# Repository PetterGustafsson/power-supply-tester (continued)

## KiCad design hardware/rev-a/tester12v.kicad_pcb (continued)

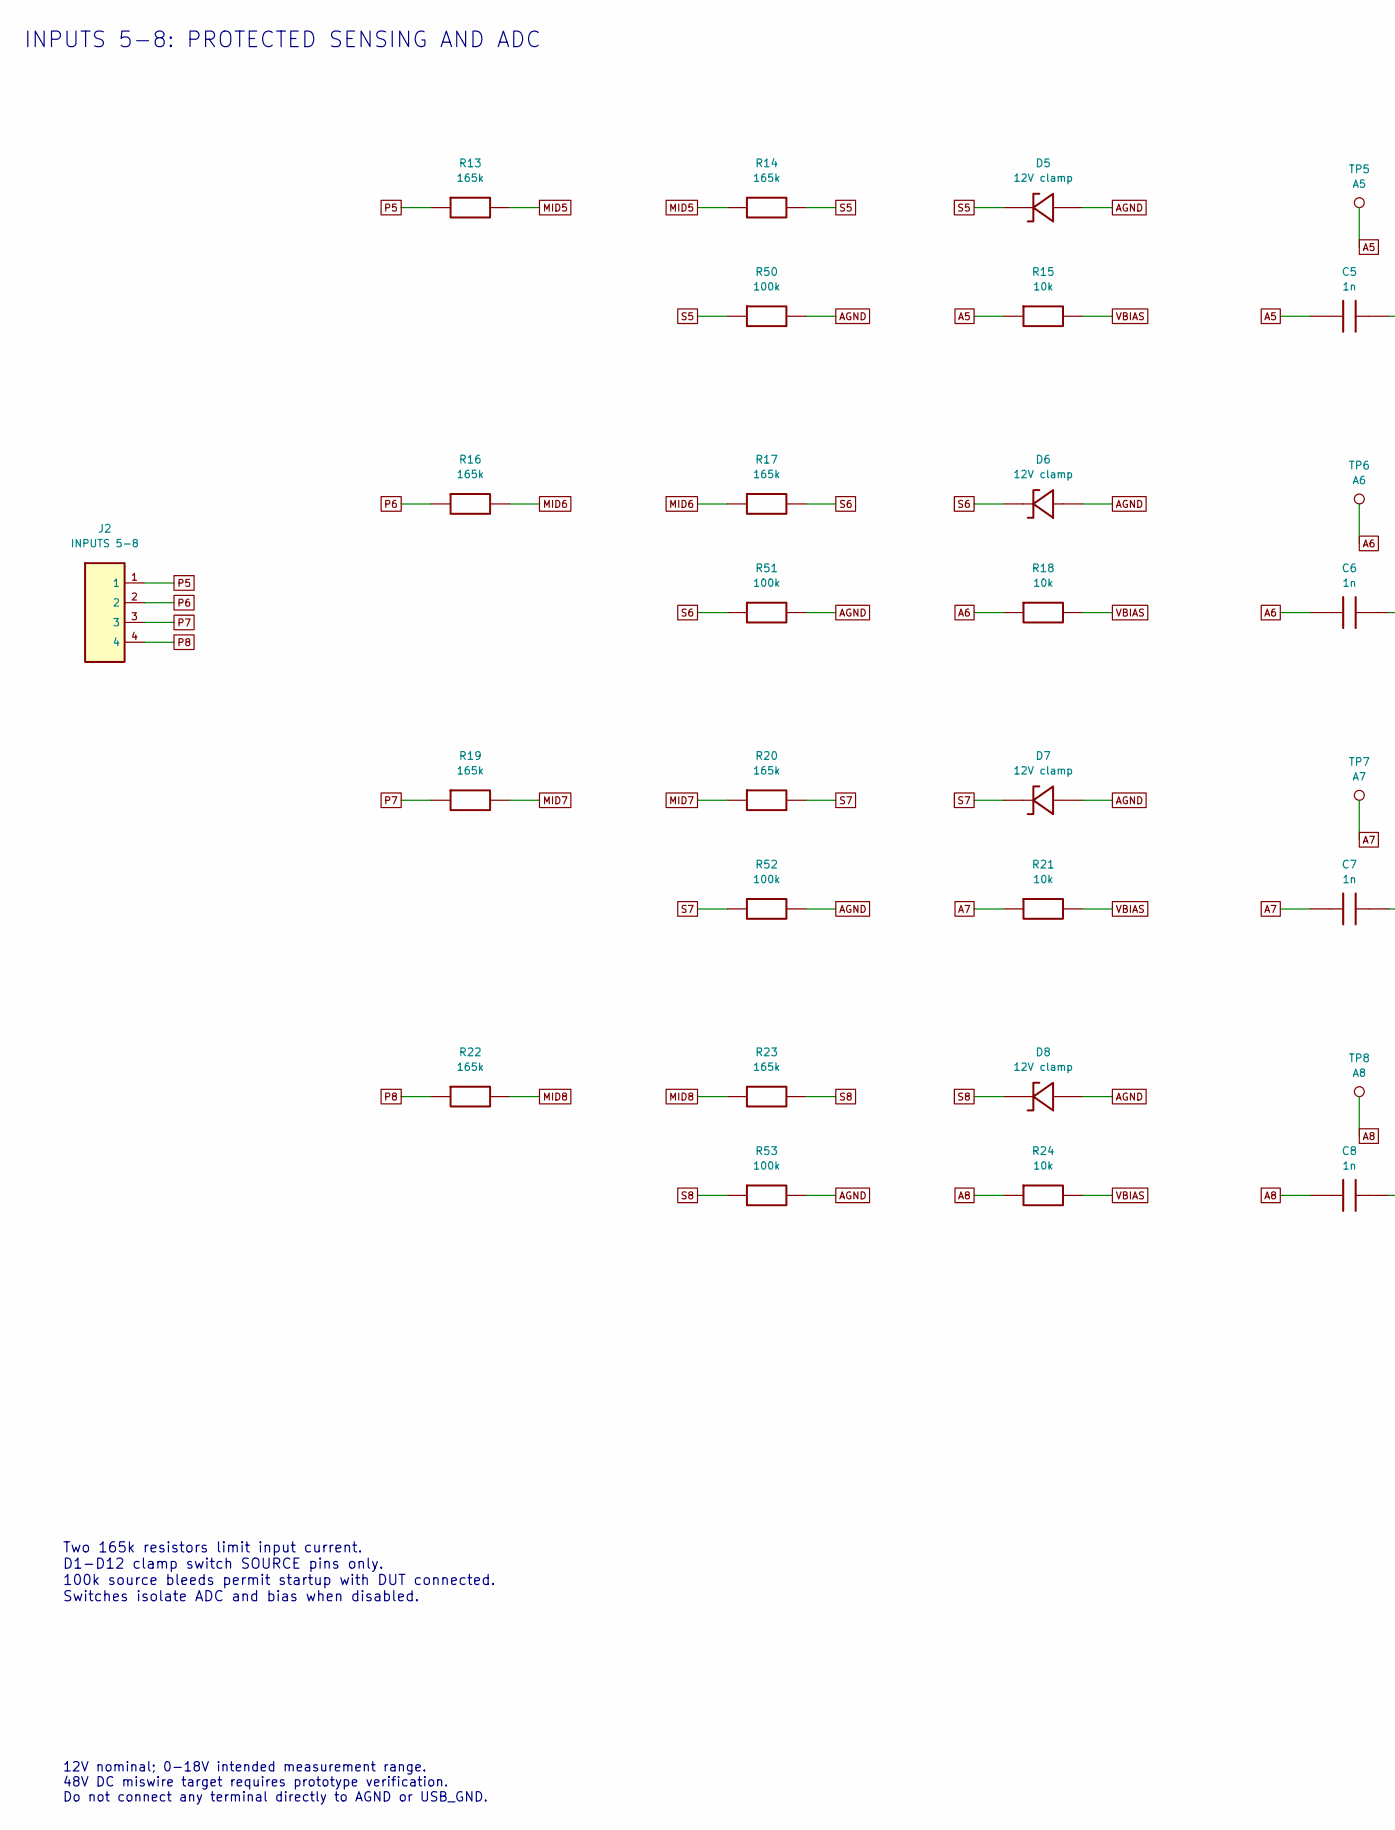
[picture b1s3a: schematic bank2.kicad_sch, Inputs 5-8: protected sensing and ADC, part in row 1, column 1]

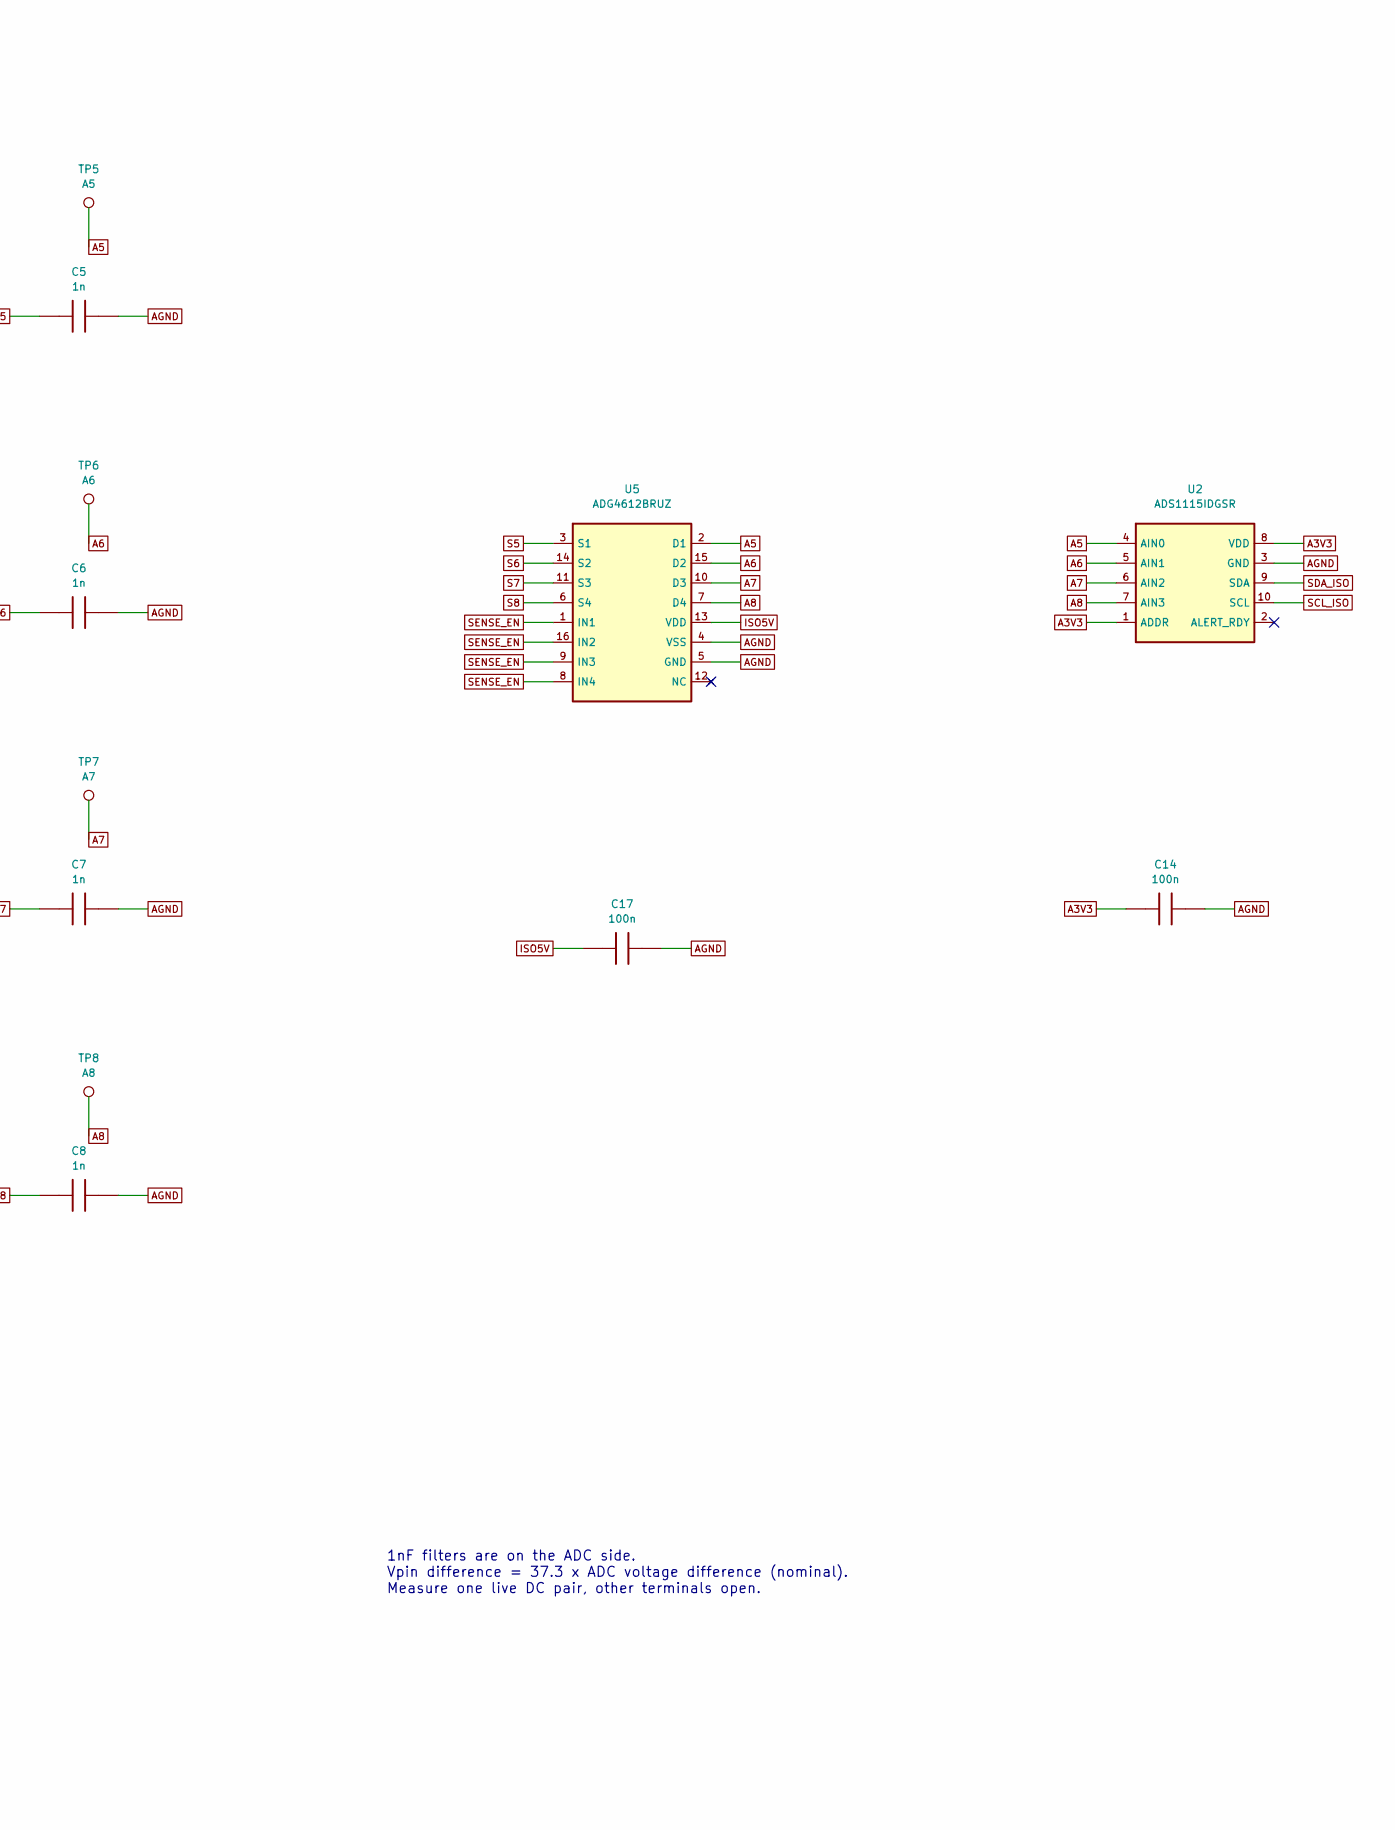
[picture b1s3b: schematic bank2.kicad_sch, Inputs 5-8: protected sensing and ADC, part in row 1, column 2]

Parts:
C5, C6, C7, C8: 1n; C_0805_2012Metric; MPN CC0805JRNPO9BN102; LCSC C62774
C14, C17: 100n; C_0805_2012Metric; MPN CC0805KRX7R9BB104; LCSC C49678
D5, D6, D7, D8: 12V clamp; D_SOD-123F; MPN BZT52H-C12,115; LCSC C282531
J2: INPUTS 5-8; TerminalBlock_Phoenix_PT-1,5-4-3.5-H_1x04_P3.50mm_Horizontal; MPN 1984633; LCSC C5144867
R13, R14, R16, R17, R19, R20, R22, R23: 165k; R_0805_2012Metric; MPN RT0805BRD07165KL; LCSC C865215
R15, R18, R21, R24: 10k; R_0805_2012Metric; MPN RT0805BRD0710KL; LCSC C110775
R50, R51, R52, R53: 100k; R_0805_2012Metric; MPN RT0805BRD07100KL; LCSC C122537
TP5: A5; TestPoint_Pad_D1.5mm
TP6: A6; TestPoint_Pad_D1.5mm
TP7: A7; TestPoint_Pad_D1.5mm
TP8: A8; TestPoint_Pad_D1.5mm
U2: ADS1115IDGSR; TSSOP-10_3x3mm_P0.5mm; MPN ADS1115IDGSR; LCSC C37593
U5: ADG4612BRUZ; TSSOP-16_4.4x5mm_P0.65mm; MPN ADG4612BRUZ-REEL7; LCSC C207399

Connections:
A3V3: C14.1, U2.1 (ADDR), U2.8 (VDD); also elsewhere on the board
A5: C5.1, R15.1, TP5.1, U2.4 (AIN0), U5.2 (D1)
A6: C6.1, R18.1, TP6.1, U2.5 (AIN1), U5.15 (D2)
A7: C7.1, R21.1, TP7.1, U2.6 (AIN2), U5.10 (D3)
A8: C8.1, R24.1, TP8.1, U2.7 (AIN3), U5.7 (D4)
AGND: C5.2, C6.2, C7.2, C8.2, C14.2, C17.2, D5.2, D6.2, D7.2, D8.2, R50.2, R51.2, R52.2, R53.2, U2.3 (GND), U5.4 (VSS), U5.5 (GND); also elsewhere on the board
ISO5V: C17.1, U5.13 (VDD); also elsewhere on the board
MID5: R13.2, R14.1
MID6: R16.2, R17.1
MID7: R19.2, R20.1
MID8: R22.2, R23.1
P5: J2.1, R13.1
P6: J2.2, R16.1
P7: J2.3, R19.1
P8: J2.4, R22.1
S5: D5.1, R14.2, R50.1, U5.3 (S1)
S6: D6.1, R17.2, R51.1, U5.14 (S2)
S7: D7.1, R20.2, R52.1, U5.11 (S3)
S8: D8.1, R23.2, R53.1, U5.6 (S4)
SCL_ISO: U2.10 (SCL); also elsewhere on the board
SDA_ISO: U2.9 (SDA); also elsewhere on the board
SENSE_EN: U5.1 (IN1), U5.8 (IN4), U5.9 (IN3), U5.16 (IN2); also elsewhere on the board
VBIAS: R15.2, R18.2, R21.2, R24.2; also elsewhere on the board

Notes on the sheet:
INPUTS 5-8: PROTECTED SENSING AND ADC
Two 165k resistors limit input current. D1-D12 clamp switch SOURCE pins only. 100k source bleeds permit startup with DUT connected. Switches isolate ADC and bias when disabled.
1nF filters are on the ADC side. Vpin difference = 37.3 x ADC voltage difference (nominal). Measure one live DC pair, other terminals open.
12V nominal; 0-18V intended measurement range. 48V DC miswire target requires prototype verification. Do not connect any terminal directly to AGND or USB_GND.

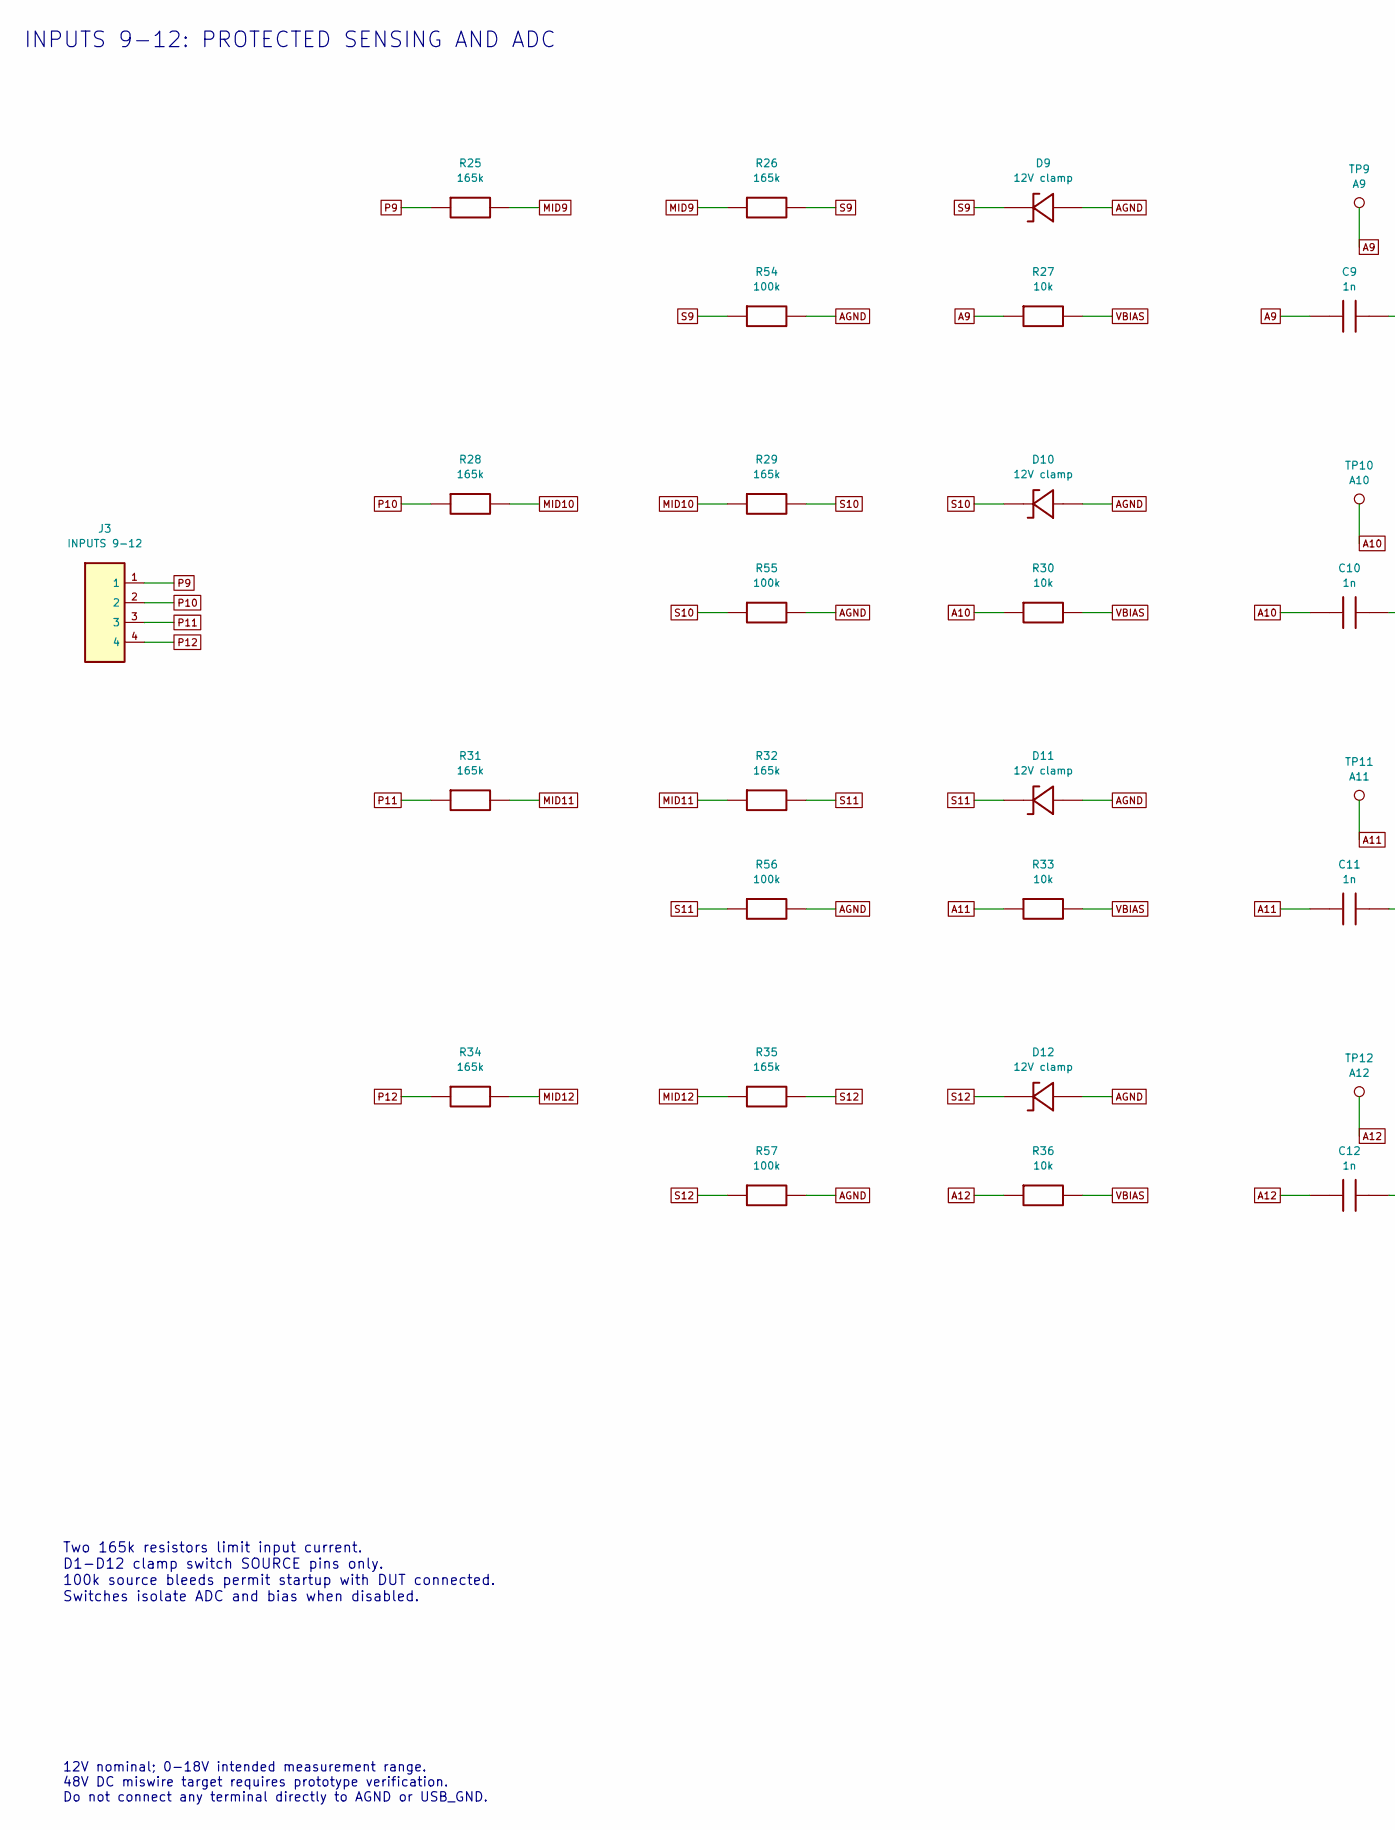
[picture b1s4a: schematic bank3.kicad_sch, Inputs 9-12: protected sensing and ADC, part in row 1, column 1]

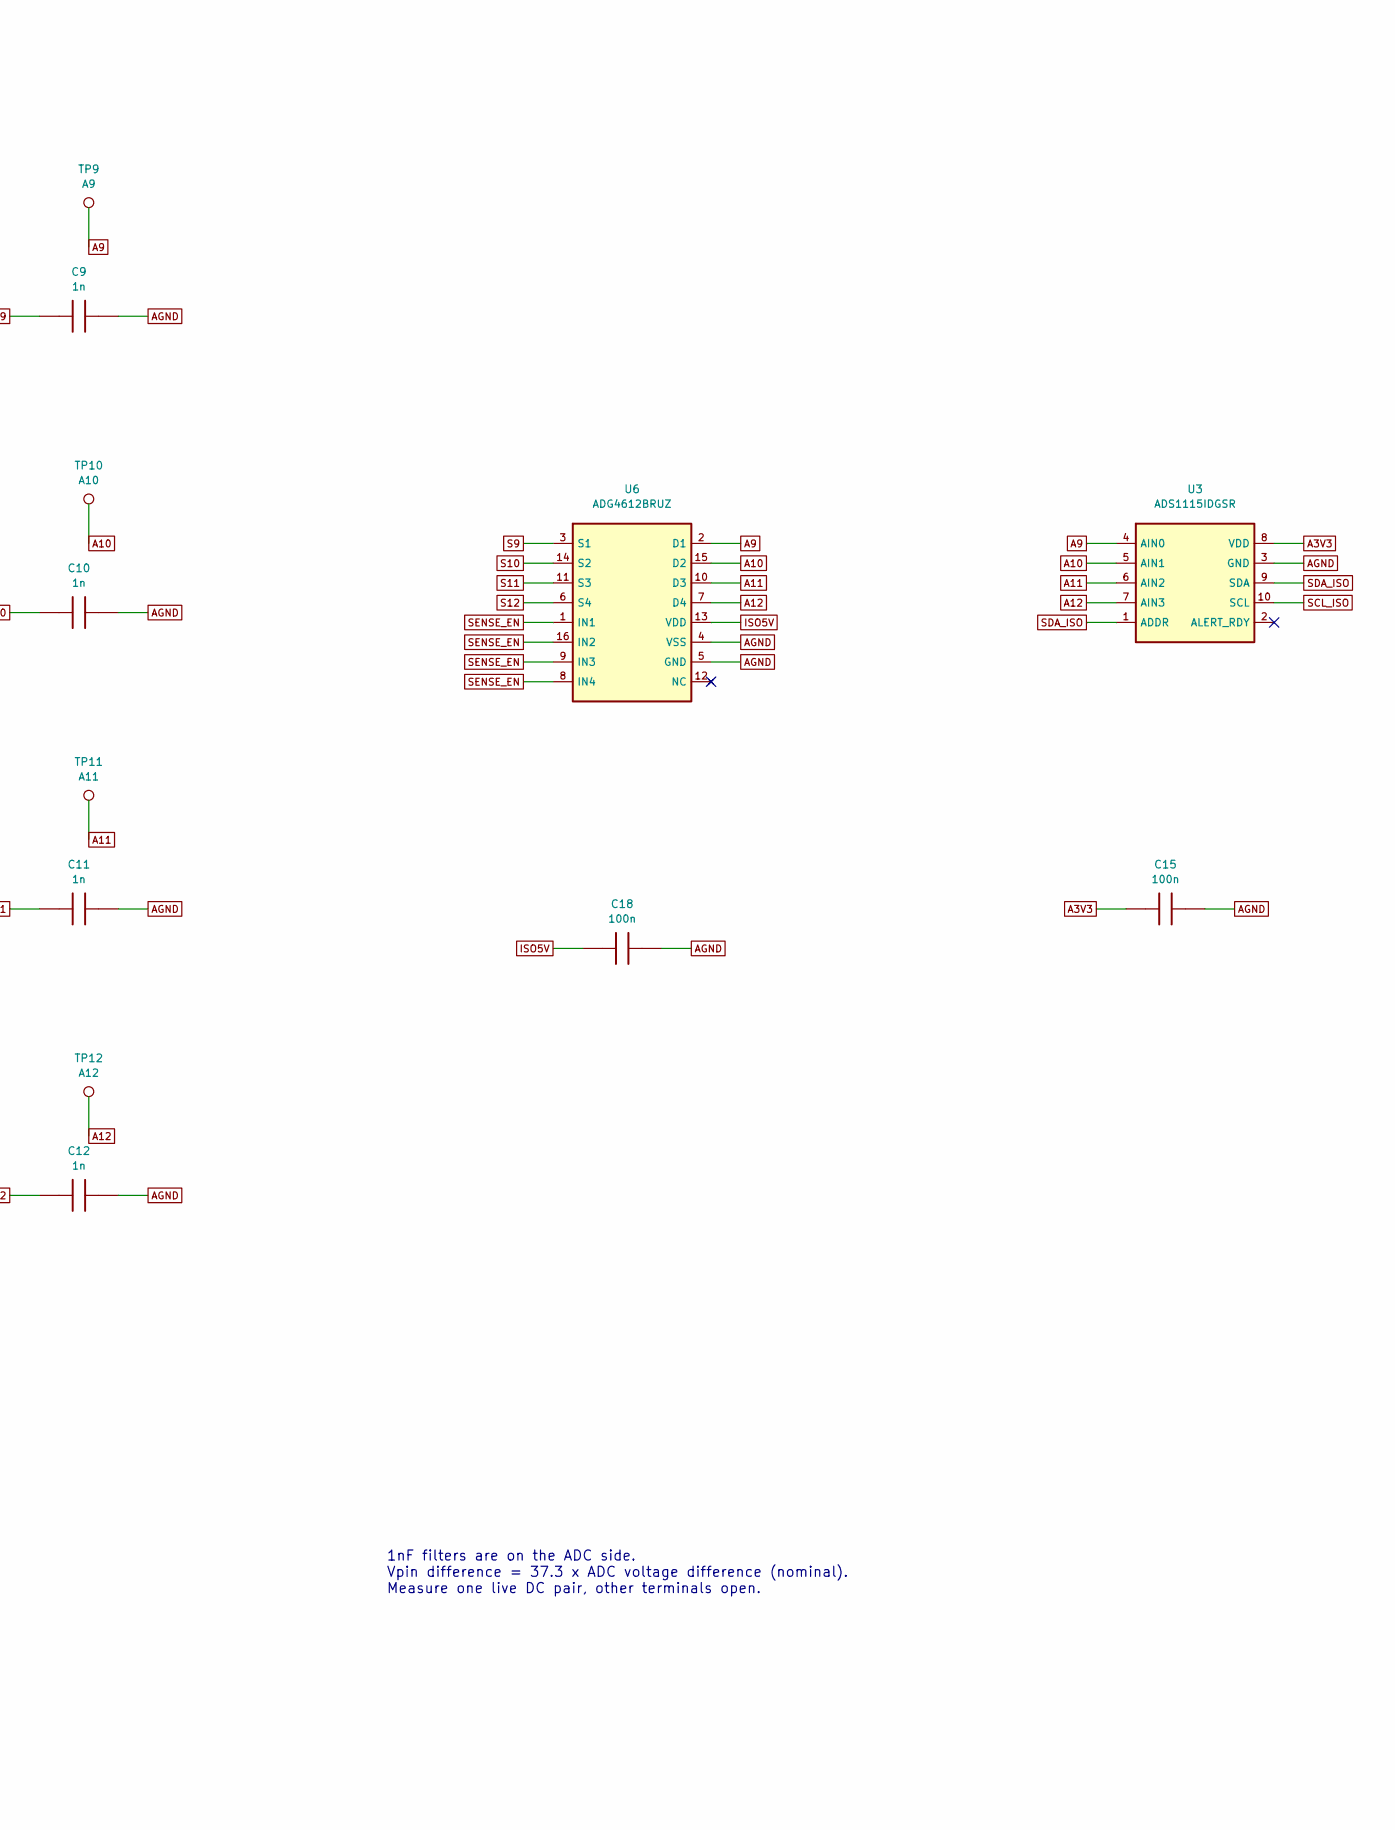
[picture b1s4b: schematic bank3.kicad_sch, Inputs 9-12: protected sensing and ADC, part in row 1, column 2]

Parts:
C9, C10, C11, C12: 1n; C_0805_2012Metric; MPN CC0805JRNPO9BN102; LCSC C62774
C15, C18: 100n; C_0805_2012Metric; MPN CC0805KRX7R9BB104; LCSC C49678
D9, D10, D11, D12: 12V clamp; D_SOD-123F; MPN BZT52H-C12,115; LCSC C282531
J3: INPUTS 9-12; TerminalBlock_Phoenix_PT-1,5-4-3.5-H_1x04_P3.50mm_Horizontal; MPN 1984633; LCSC C5144867
R25, R26, R28, R29, R31, R32, R34, R35: 165k; R_0805_2012Metric; MPN RT0805BRD07165KL; LCSC C865215
R27, R30, R33, R36: 10k; R_0805_2012Metric; MPN RT0805BRD0710KL; LCSC C110775
R54, R55, R56, R57: 100k; R_0805_2012Metric; MPN RT0805BRD07100KL; LCSC C122537
TP9: A9; TestPoint_Pad_D1.5mm
TP10: A10; TestPoint_Pad_D1.5mm
TP11: A11; TestPoint_Pad_D1.5mm
TP12: A12; TestPoint_Pad_D1.5mm
U3: ADS1115IDGSR; TSSOP-10_3x3mm_P0.5mm; MPN ADS1115IDGSR; LCSC C37593
U6: ADG4612BRUZ; TSSOP-16_4.4x5mm_P0.65mm; MPN ADG4612BRUZ-REEL7; LCSC C207399

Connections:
A3V3: C15.1, U3.8 (VDD); also elsewhere on the board
A9: C9.1, R27.1, TP9.1, U3.4 (AIN0), U6.2 (D1)
A10: C10.1, R30.1, TP10.1, U3.5 (AIN1), U6.15 (D2)
A11: C11.1, R33.1, TP11.1, U3.6 (AIN2), U6.10 (D3)
A12: C12.1, R36.1, TP12.1, U3.7 (AIN3), U6.7 (D4)
AGND: C9.2, C10.2, C11.2, C12.2, C15.2, C18.2, D9.2, D10.2, D11.2, D12.2, R54.2, R55.2, R56.2, R57.2, U3.3 (GND), U6.4 (VSS), U6.5 (GND); also elsewhere on the board
ISO5V: C18.1, U6.13 (VDD); also elsewhere on the board
MID9: R25.2, R26.1
MID10: R28.2, R29.1
MID11: R31.2, R32.1
MID12: R34.2, R35.1
P9: J3.1, R25.1
P10: J3.2, R28.1
P11: J3.3, R31.1
P12: J3.4, R34.1
S9: D9.1, R26.2, R54.1, U6.3 (S1)
S10: D10.1, R29.2, R55.1, U6.14 (S2)
S11: D11.1, R32.2, R56.1, U6.11 (S3)
S12: D12.1, R35.2, R57.1, U6.6 (S4)
SCL_ISO: U3.10 (SCL); also elsewhere on the board
SDA_ISO: U3.1 (ADDR), U3.9 (SDA); also elsewhere on the board
SENSE_EN: U6.1 (IN1), U6.8 (IN4), U6.9 (IN3), U6.16 (IN2); also elsewhere on the board
VBIAS: R27.2, R30.2, R33.2, R36.2; also elsewhere on the board

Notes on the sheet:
INPUTS 9-12: PROTECTED SENSING AND ADC
Two 165k resistors limit input current. D1-D12 clamp switch SOURCE pins only. 100k source bleeds permit startup with DUT connected. Switches isolate ADC and bias when disabled.
1nF filters are on the ADC side. Vpin difference = 37.3 x ADC voltage difference (nominal). Measure one live DC pair, other terminals open.
12V nominal; 0-18V intended measurement range. 48V DC miswire target requires prototype verification. Do not connect any terminal directly to AGND or USB_GND.

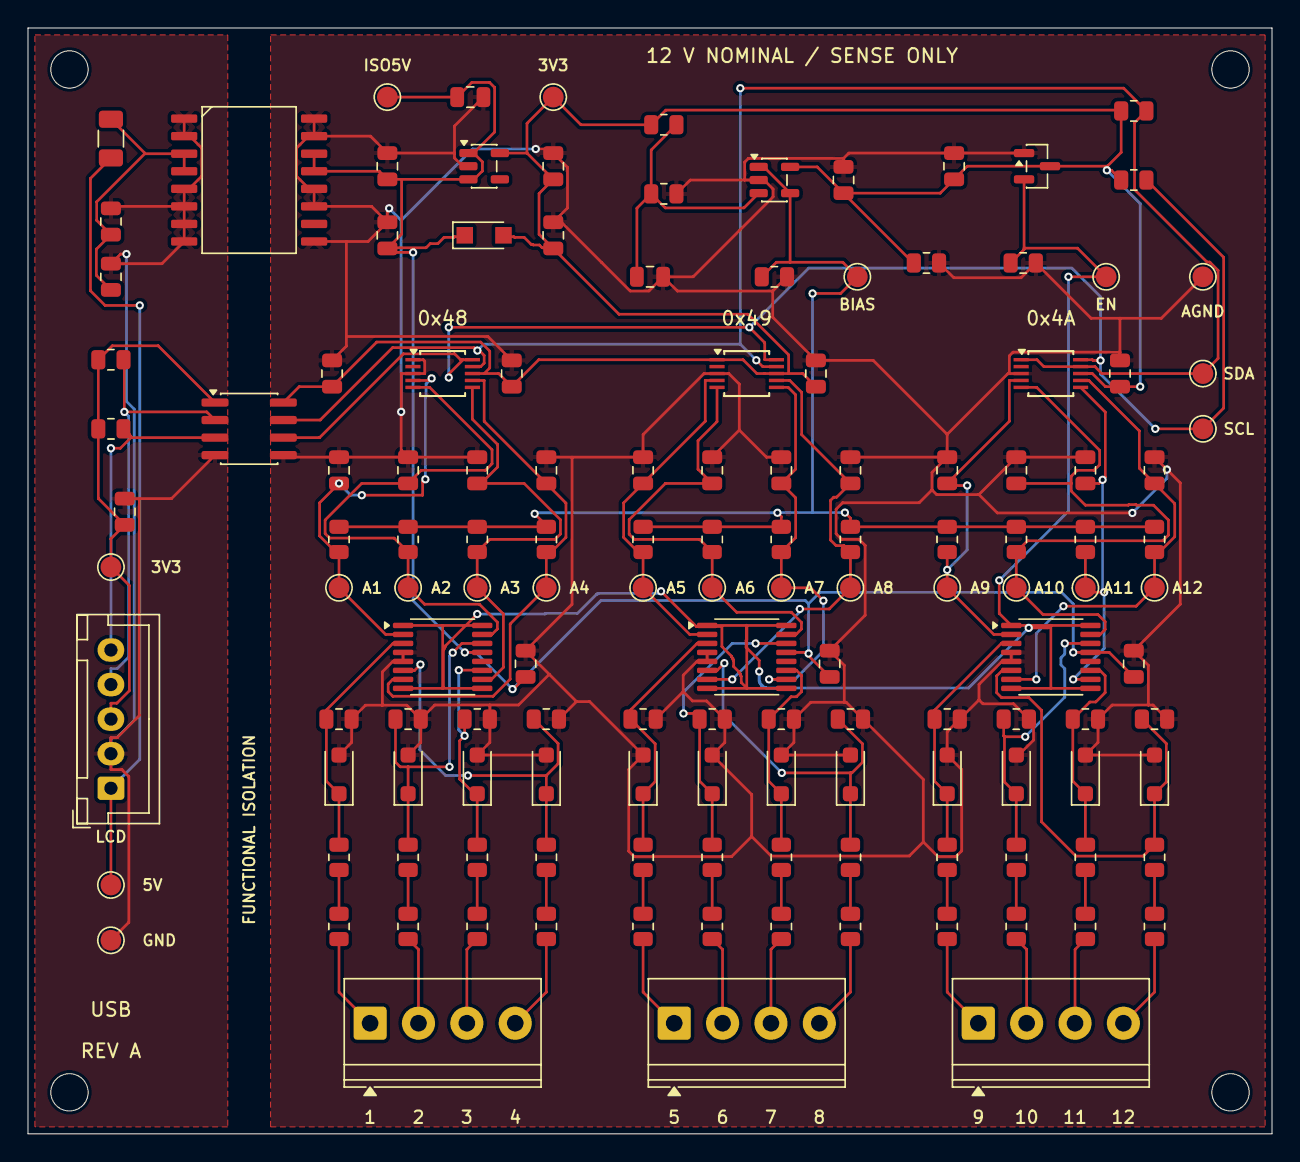
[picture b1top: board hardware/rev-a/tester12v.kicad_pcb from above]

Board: 2 copper layers, 90.0 x 80.0 mm, 142 parts (0 on the bottom side), 62 nets.

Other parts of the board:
H1, H2, H3, H4: MountingHole_2.7mm_M2.5

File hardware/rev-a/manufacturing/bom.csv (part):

Reference,Value,Manufacturer,MPN,Footprint,Populate,Notes,LCSC,JLC Category
J1,INPUTS 1-4,Phoenix Contact,1984633,"Tester:TerminalBlock_Phoenix_PT-1,5-4-3.5-H_1x04_P3.50mm_Horizontal",YES,"PT 1,5/4-3,5-H; 1984633 verified against Phoenix Contact product page, 3.5mm pitch",C5144867,Extended
R1,165k,Yageo,RT0805BRD07165KL,Tester:R_0805_2012Metric,YES,"0.1%, 25 ppm/K",C865215,Extended
R2,165k,Yageo,RT0805BRD07165KL,Tester:R_0805_2012Metric,YES,"0.1%, 25 ppm/K",C865215,Extended
D1,12V clamp,Nexperia,"BZT52H-C12,115",Tester:D_SOD-123F,YES,Clamp is before power-off switch; not an ADC rail clamp,C282531,Extended
R3,10k,Yageo,RT0805BRD0710KL,Tester:R_0805_2012Metric,YES,"0.1%, 25 ppm/K",C110775,Extended
R46,100k,Yageo,RT0805BRD07100KL,Tester:R_0805_2012Metric,YES,"0.1%, 25 ppm/K",C122537,Extended
C1,1n,Yageo,CC0805JRNPO9BN102,Tester:C_0805_2012Metric,YES,"Use specified capacitance, voltage and dielectric | JLC: Stocked replacement; 1nF, 5%, 50V, C0G/NP0 preserved",C62774,Extended
R4,165k,Yageo,RT0805BRD07165KL,Tester:R_0805_2012Metric,YES,"0.1%, 25 ppm/K",C865215,Extended
R5,165k,Yageo,RT0805BRD07165KL,Tester:R_0805_2012Metric,YES,"0.1%, 25 ppm/K",C865215,Extended
D2,12V clamp,Nexperia,"BZT52H-C12,115",Tester:D_SOD-123F,YES,Clamp is before power-off switch; not an ADC rail clamp,C282531,Extended
R6,10k,Yageo,RT0805BRD0710KL,Tester:R_0805_2012Metric,YES,"0.1%, 25 ppm/K",C110775,Extended
R47,100k,Yageo,RT0805BRD07100KL,Tester:R_0805_2012Metric,YES,"0.1%, 25 ppm/K",C122537,Extended
C2,1n,Yageo,CC0805JRNPO9BN102,Tester:C_0805_2012Metric,YES,"Use specified capacitance, voltage and dielectric | JLC: Stocked replacement; 1nF, 5%, 50V, C0G/NP0 preserved",C62774,Extended
R7,165k,Yageo,RT0805BRD07165KL,Tester:R_0805_2012Metric,YES,"0.1%, 25 ppm/K",C865215,Extended
R8,165k,Yageo,RT0805BRD07165KL,Tester:R_0805_2012Metric,YES,"0.1%, 25 ppm/K",C865215,Extended
D3,12V clamp,Nexperia,"BZT52H-C12,115",Tester:D_SOD-123F,YES,Clamp is before power-off switch; not an ADC rail clamp,C282531,Extended
R9,10k,Yageo,RT0805BRD0710KL,Tester:R_0805_2012Metric,YES,"0.1%, 25 ppm/K",C110775,Extended
R48,100k,Yageo,RT0805BRD07100KL,Tester:R_0805_2012Metric,YES,"0.1%, 25 ppm/K",C122537,Extended
C3,1n,Yageo,CC0805JRNPO9BN102,Tester:C_0805_2012Metric,YES,"Use specified capacitance, voltage and dielectric | JLC: Stocked replacement; 1nF, 5%, 50V, C0G/NP0 preserved",C62774,Extended
R10,165k,Yageo,RT0805BRD07165KL,Tester:R_0805_2012Metric,YES,"0.1%, 25 ppm/K",C865215,Extended
R11,165k,Yageo,RT0805BRD07165KL,Tester:R_0805_2012Metric,YES,"0.1%, 25 ppm/K",C865215,Extended
D4,12V clamp,Nexperia,"BZT52H-C12,115",Tester:D_SOD-123F,YES,Clamp is before power-off switch; not an ADC rail clamp,C282531,Extended
R12,10k,Yageo,RT0805BRD0710KL,Tester:R_0805_2012Metric,YES,"0.1%, 25 ppm/K",C110775,Extended
R49,100k,Yageo,RT0805BRD07100KL,Tester:R_0805_2012Metric,YES,"0.1%, 25 ppm/K",C122537,Extended
C4,1n,Yageo,CC0805JRNPO9BN102,Tester:C_0805_2012Metric,YES,"Use specified capacitance, voltage and dielectric | JLC: Stocked replacement; 1nF, 5%, 50V, C0G/NP0 preserved",C62774,Extended
U1,ADS1115IDGSR,Texas Instruments,ADS1115IDGSR,Tester:TSSOP-10_3x3mm_P0.5mm,YES,ADDR=GND/3V3/SDA for 0x48/0x49/0x4A,C37593,Extended
U4,ADG4612BRUZ,Analog Devices,ADG4612BRUZ-REEL7,Tester:TSSOP-16_4.4x5mm_P0.65mm,YES,"TSSOP-16; powered from isolated 5V; enable from 3.08V supervisor | JLC: In-stock tape-and-reel packaging; same silicon, pinout and TSSOP-16",C207399,Extended
C13,100n,Yageo,CC0805KRX7R9BB104,Tester:C_0805_2012Metric,YES,"Use specified capacitance, voltage and dielectric | JLC: Basic; 100nF, 10%, 50V, X7R preserved",C49678,Basic
C16,100n,Yageo,CC0805KRX7R9BB104,Tester:C_0805_2012Metric,YES,"Use specified capacitance, voltage and dielectric | JLC: Basic; 100nF, 10%, 50V, X7R preserved",C49678,Basic
J2,INPUTS 5-8,Phoenix Contact,1984633,"Tester:TerminalBlock_Phoenix_PT-1,5-4-3.5-H_1x04_P3.50mm_Horizontal",YES,"PT 1,5/4-3,5-H; 1984633 verified against Phoenix Contact product page, 3.5mm pitch",C5144867,Extended
R13,165k,Yageo,RT0805BRD07165KL,Tester:R_0805_2012Metric,YES,"0.1%, 25 ppm/K",C865215,Extended
R14,165k,Yageo,RT0805BRD07165KL,Tester:R_0805_2012Metric,YES,"0.1%, 25 ppm/K",C865215,Extended
D5,12V clamp,Nexperia,"BZT52H-C12,115",Tester:D_SOD-123F,YES,Clamp is before power-off switch; not an ADC rail clamp,C282531,Extended
R15,10k,Yageo,RT0805BRD0710KL,Tester:R_0805_2012Metric,YES,"0.1%, 25 ppm/K",C110775,Extended
R50,100k,Yageo,RT0805BRD07100KL,Tester:R_0805_2012Metric,YES,"0.1%, 25 ppm/K",C122537,Extended
C5,1n,Yageo,CC0805JRNPO9BN102,Tester:C_0805_2012Metric,YES,"Use specified capacitance, voltage and dielectric | JLC: Stocked replacement; 1nF, 5%, 50V, C0G/NP0 preserved",C62774,Extended
R16,165k,Yageo,RT0805BRD07165KL,Tester:R_0805_2012Metric,YES,"0.1%, 25 ppm/K",C865215,Extended
R17,165k,Yageo,RT0805BRD07165KL,Tester:R_0805_2012Metric,YES,"0.1%, 25 ppm/K",C865215,Extended
D6,12V clamp,Nexperia,"BZT52H-C12,115",Tester:D_SOD-123F,YES,Clamp is before power-off switch; not an ADC rail clamp,C282531,Extended
R18,10k,Yageo,RT0805BRD0710KL,Tester:R_0805_2012Metric,YES,"0.1%, 25 ppm/K",C110775,Extended
R51,100k,Yageo,RT0805BRD07100KL,Tester:R_0805_2012Metric,YES,"0.1%, 25 ppm/K",C122537,Extended
C6,1n,Yageo,CC0805JRNPO9BN102,Tester:C_0805_2012Metric,YES,"Use specified capacitance, voltage and dielectric | JLC: Stocked replacement; 1nF, 5%, 50V, C0G/NP0 preserved",C62774,Extended
R19,165k,Yageo,RT0805BRD07165KL,Tester:R_0805_2012Metric,YES,"0.1%, 25 ppm/K",C865215,Extended
R20,165k,Yageo,RT0805BRD07165KL,Tester:R_0805_2012Metric,YES,"0.1%, 25 ppm/K",C865215,Extended
D7,12V clamp,Nexperia,"BZT52H-C12,115",Tester:D_SOD-123F,YES,Clamp is before power-off switch; not an ADC rail clamp,C282531,Extended
R21,10k,Yageo,RT0805BRD0710KL,Tester:R_0805_2012Metric,YES,"0.1%, 25 ppm/K",C110775,Extended
R52,100k,Yageo,RT0805BRD07100KL,Tester:R_0805_2012Metric,YES,"0.1%, 25 ppm/K",C122537,Extended
C7,1n,Yageo,CC0805JRNPO9BN102,Tester:C_0805_2012Metric,YES,"Use specified capacitance, voltage and dielectric | JLC: Stocked replacement; 1nF, 5%, 50V, C0G/NP0 preserved",C62774,Extended
R22,165k,Yageo,RT0805BRD07165KL,Tester:R_0805_2012Metric,YES,"0.1%, 25 ppm/K",C865215,Extended
R23,165k,Yageo,RT0805BRD07165KL,Tester:R_0805_2012Metric,YES,"0.1%, 25 ppm/K",C865215,Extended
D8,12V clamp,Nexperia,"BZT52H-C12,115",Tester:D_SOD-123F,YES,Clamp is before power-off switch; not an ADC rail clamp,C282531,Extended
R24,10k,Yageo,RT0805BRD0710KL,Tester:R_0805_2012Metric,YES,"0.1%, 25 ppm/K",C110775,Extended
R53,100k,Yageo,RT0805BRD07100KL,Tester:R_0805_2012Metric,YES,"0.1%, 25 ppm/K",C122537,Extended
C8,1n,Yageo,CC0805JRNPO9BN102,Tester:C_0805_2012Metric,YES,"Use specified capacitance, voltage and dielectric | JLC: Stocked replacement; 1nF, 5%, 50V, C0G/NP0 preserved",C62774,Extended
U2,ADS1115IDGSR,Texas Instruments,ADS1115IDGSR,Tester:TSSOP-10_3x3mm_P0.5mm,YES,ADDR=GND/3V3/SDA for 0x48/0x49/0x4A,C37593,Extended
U5,ADG4612BRUZ,Analog Devices,ADG4612BRUZ-REEL7,Tester:TSSOP-16_4.4x5mm_P0.65mm,YES,"TSSOP-16; powered from isolated 5V; enable from 3.08V supervisor | JLC: In-stock tape-and-reel packaging; same silicon, pinout and TSSOP-16",C207399,Extended
C14,100n,Yageo,CC0805KRX7R9BB104,Tester:C_0805_2012Metric,YES,"Use specified capacitance, voltage and dielectric | JLC: Basic; 100nF, 10%, 50V, X7R preserved",C49678,Basic
C17,100n,Yageo,CC0805KRX7R9BB104,Tester:C_0805_2012Metric,YES,"Use specified capacitance, voltage and dielectric | JLC: Basic; 100nF, 10%, 50V, X7R preserved",C49678,Basic
J3,INPUTS 9-12,Phoenix Contact,1984633,"Tester:TerminalBlock_Phoenix_PT-1,5-4-3.5-H_1x04_P3.50mm_Horizontal",YES,"PT 1,5/4-3,5-H; 1984633 verified against Phoenix Contact product page, 3.5mm pitch",C5144867,Extended
R25,165k,Yageo,RT0805BRD07165KL,Tester:R_0805_2012Metric,YES,"0.1%, 25 ppm/K",C865215,Extended
R26,165k,Yageo,RT0805BRD07165KL,Tester:R_0805_2012Metric,YES,"0.1%, 25 ppm/K",C865215,Extended
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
